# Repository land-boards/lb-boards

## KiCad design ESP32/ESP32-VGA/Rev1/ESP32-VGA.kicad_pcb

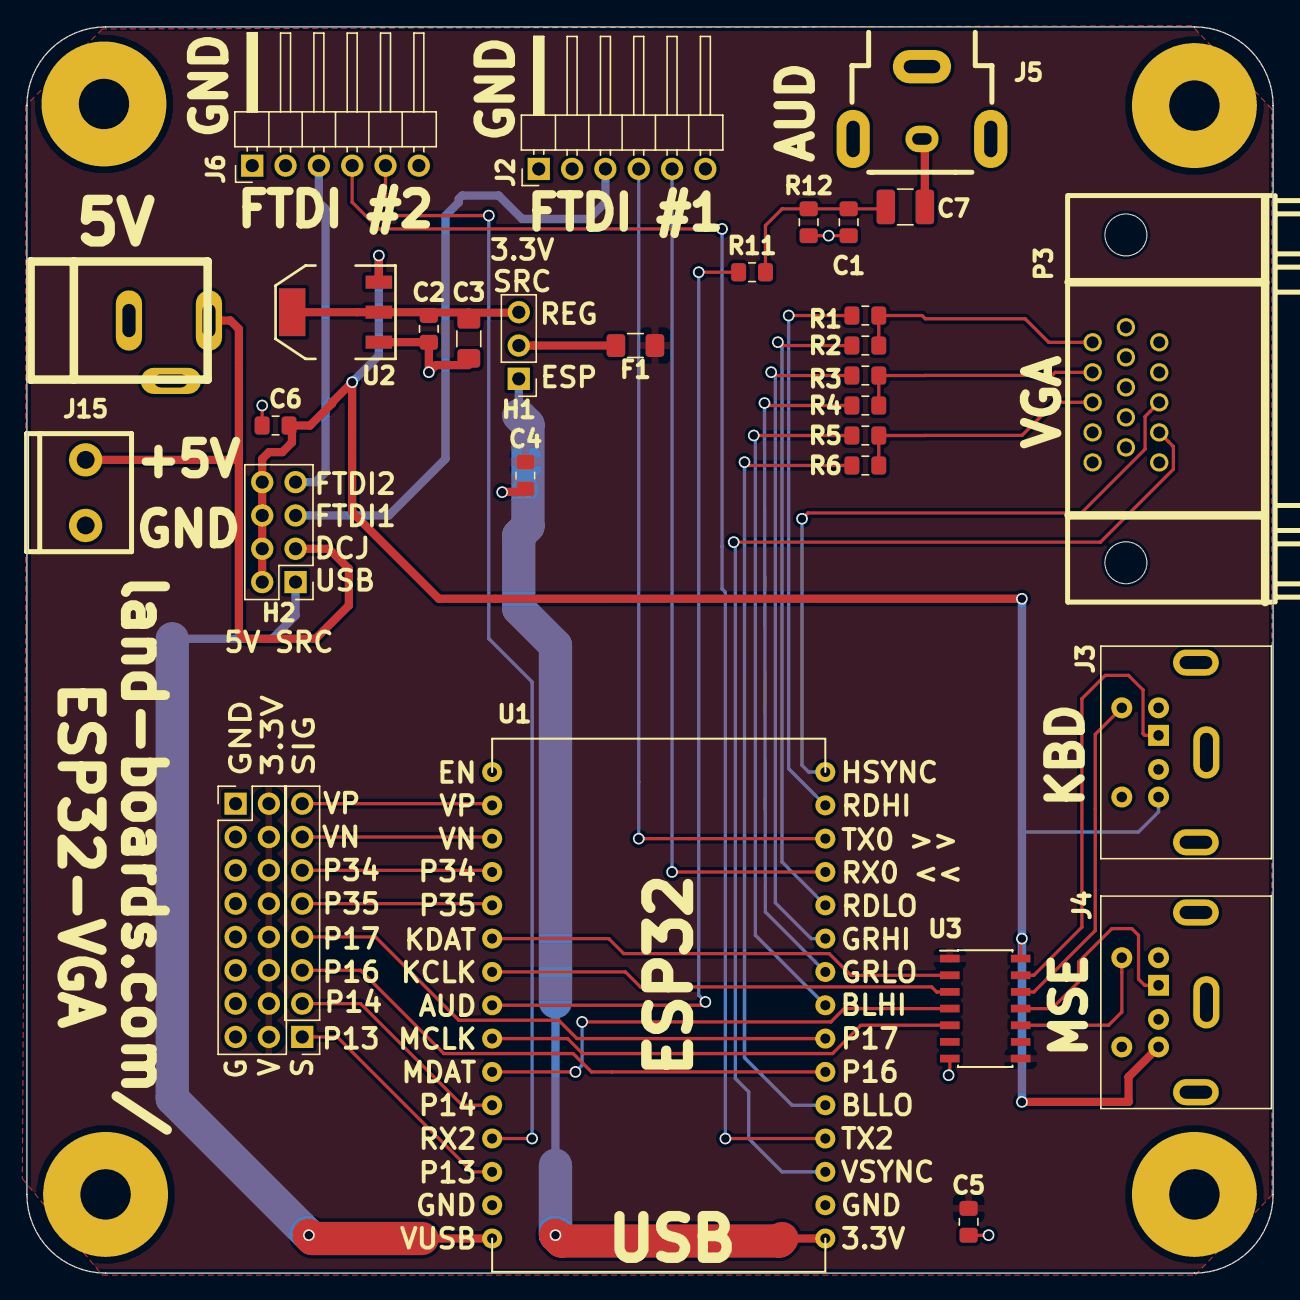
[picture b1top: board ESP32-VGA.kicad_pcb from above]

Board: 2 copper layers, 95.0 x 95.0 mm, 36 parts (0 on the bottom side), 44 nets.

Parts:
C1, C2, C4, C5, C6: 0.1uF; C_0805_2012Metric_Pad1.15x1.40mm_HandSolder
C3: 10uF; C_1206_3216Metric_Pad1.42x1.75mm_HandSolder
C7: CP1; C_1210_3225Metric_Pad1.42x2.65mm_HandSolder
F1: Polyfuse_Small; Fuse_1206_3216Metric_Pad1.42x1.75mm_HandSolder
H1: Conn_01x03; PinHeader_1x03_P2.54mm_Vertical
H2: Conn_02x04_Odd_Even; PinHeader_2x04_P2.54mm_Vertical
J1: DCJ0202; DCJ-NEW-Slotted
J2, J6: FTDI; PinHeader_1x06_P2.54mm_Horizontal
J3, J4: PS2_DIN6; Connector_Mini-DIN_Female_6Pin_2rows
J5: RCA-JACK; RCA
J15: Conn_01x02; TB2-5MM
MTG1, MTG2, MTG3: MTG_HOLE; MTG-6-32
MTG?1: MTG_HOLE; MTG-6-32
P2: Conn_02x08_Odd_Even; PinHeader_2x08_P2.54mm_Vertical
P3: VGA; DB_15F-VGA-fixed
P4: Conn_01x08; PinHeader_1x08_P2.54mm_Vertical
R1, R3, R5: 523; R_0805_2012Metric_Pad1.15x1.40mm_HandSolder
R2, R4, R6: 261; R_0805_2012Metric_Pad1.15x1.40mm_HandSolder
R11: 270; R_0805_2012Metric_Pad1.15x1.40mm_HandSolder
R12: 150; R_0805_2012Metric_Pad1.15x1.40mm_HandSolder
TEST1: COUPON; TEST_BLK-REAR
U1: ESP32; ESP32_EXP
U2: AP1117; SOT223
U3: TXS0104; SOIC-14_3.9x8.7mm_P1.27mm

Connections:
+3V3: C4.1, C5.1, F1.1, P2.2, P2.4, P2.6, P2.8, P2.10, P2.12, P2.14, P2.16, U3.1, U3.8
+5V: C6.1, H2.2, H2.4, H2.6, H2.8, J3.4, J4.4, U2.3, U3.14
/AUDIO: R11.2, U1.23
/BLUHI: R6.2, U1.5
/BLULO: R5.2, U1.8
/DCIN: H2.3, J1.1, J15.2
/ESP3V: H1.1, U1.1
/FTDI5V0: H2.5, J2.3
/FTDI5V2: H2.7, J6.3
/GP13: P4.1, U1.28
/GP14: P4.2, U1.26
/GP16: P4.3, U1.6
/GP17: P4.4, U1.7
/GP34: P4.6, U1.19
/GP35: P4.5, U1.20
/GRNHI: R4.2, U1.9
/GRNLO: R3.2, U1.10
/HSYNC: P3.13, U1.15
/KBCLK: U1.22, U3.3
/KBDAT: U1.21, U3.2
/MSECLK: U1.24, U3.5
/MSEDAT: U1.25, U3.4
/REDHI: R2.2, U1.11
/REDLO: R1.2, U1.14
/RX0: J2.5, U1.12
/RX2: J6.5, U1.27
/TX0: J2.4, U1.13
/TX2: J6.4, U1.4
/VN: P4.7, U1.18
/VO3: C2.1, C3.1, H1.3, U2.2, U2.4
/VP: P4.8, U1.17
/VSYNC: P3.14, U1.3
/VUSB: H2.1, U1.30
GND: C1.2, C2.2, C3.2, C4.2, C5.2, C6.2, J1.2, J1.3, J2.1, J3.3, J4.3, J5.1, J5.2, J5.3, J6.1, J15.1, P2.1, P2.3, P2.5, P2.7, P2.9, P2.11, P2.13, P2.15, P3.5, P3.6, P3.7, P3.8, P3.10, R12.1, U1.2, U1.29, U2.1, U3.7
unnamed: C1.1, C7.1, R11.1, R12.2
unnamed: C7.2, J5.4
unnamed: F1.2, H1.2
unnamed: J3.1, U3.13
unnamed: J3.5, U3.12
unnamed: J4.1, U3.11
unnamed: J4.5, U3.10
unnamed: P3.1, R1.1, R2.1
unnamed: P3.2, R3.1, R4.1
unnamed: P3.3, R5.1, R6.1

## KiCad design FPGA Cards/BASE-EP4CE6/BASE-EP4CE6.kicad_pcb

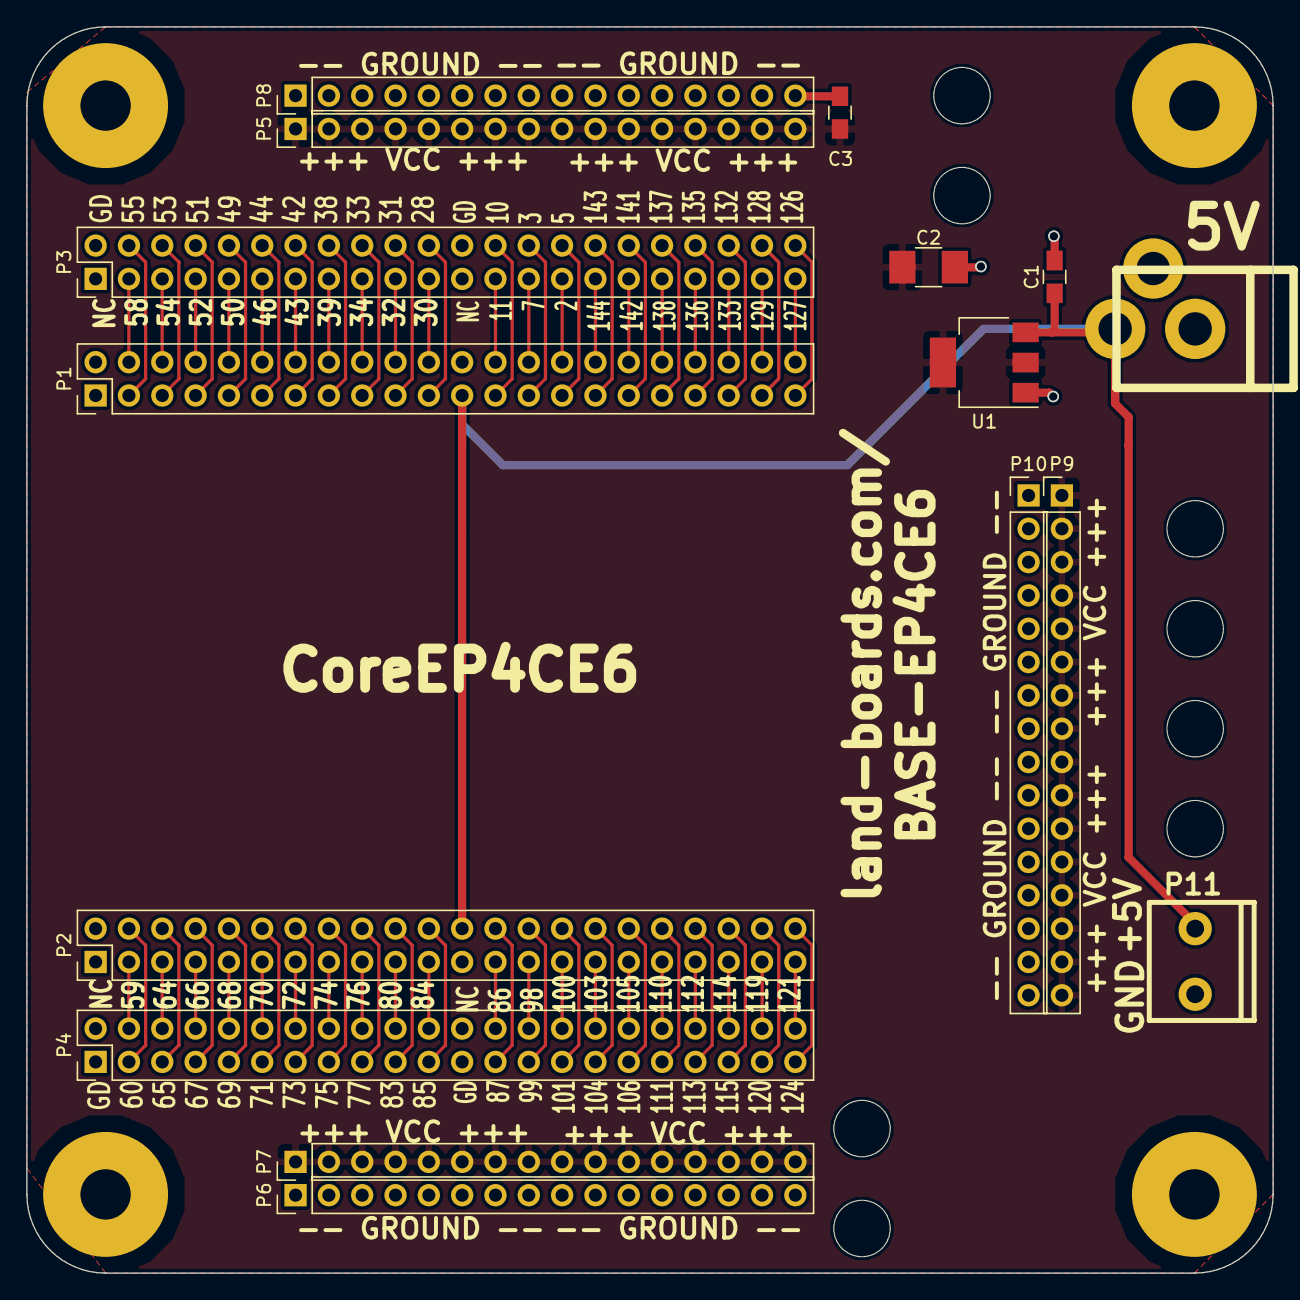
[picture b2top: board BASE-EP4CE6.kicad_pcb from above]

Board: 2 copper layers, 95.0 x 95.0 mm, 30 parts (0 on the bottom side), 83 nets.

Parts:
C1, C3: 0.1uF; C_0805_HandSoldering
C2: 10uF; C_1210_HandSoldering
COUP?1: COUPON; TEST_BLK-REAR
J1: DCJ0202; DCJ-NEW
MTG1, MTG2, MTG3: MTG_HOLE; MTG-6-32
MTG6, MTG7, MTG9, MTG10, MTG12, MTG13, MTG14, MTG15: MTG_HOLE; MountingHole_4.3mm_M4
MTG?1: MTG_HOLE; MTG-6-32
P1, P2, P3, P4: CONN_02X22; Pin_Header_Straight_2x22_Pitch2.54mm
P5, P6, P7, P8, P9, P10: CONN_01X16; Pin_Header_Straight_1x16_Pitch2.54mm
P11: CONN_01X02; TB2-5MM
TEST: COUPON; TEST_BLK-REAR
U1: AP1117; SOT-223

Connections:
+3V3: C2.1, C3.1, P5.1, P5.2, P5.3, P5.4, P5.5, P5.6, P5.7, P5.8, P5.9, P5.10, P5.11, P5.12, P5.13, P5.14, P5.15, P5.16, P7.1, P7.2, P7.3, P7.4, P7.5, P7.6, P7.7, P7.8, P7.9, P7.10, P7.11, P7.12, P7.13, P7.14, P7.15, P7.16, P9.1, P9.2, P9.3, P9.4, P9.5, P9.6, P9.7, P9.8, P9.9, P9.10, P9.11, P9.12, P9.13, P9.14, P9.15, P9.16, U1.2, U1.4
+5V: C1.1, J1.1, P1.23, P2.24, P11.1, U1.3
/P2: P1.30, P3.29
/P3: P1.27, P3.28
/P5: P1.29, P3.30
/P7: P1.28, P3.27
/P10: P1.25, P3.26
/P11: P1.26, P3.25
/P28: P1.21, P3.22
/P30: P1.22, P3.21
/P31: P1.19, P3.20
/P32: P1.20, P3.19
/P33: P1.17, P3.18
/P34: P1.18, P3.17
/P38: P1.15, P3.16
/P39: P1.16, P3.15
/P42: P1.13, P3.14
/P43: P1.14, P3.13
/P44: P1.11, P3.12
/P46: P1.12, P3.11
/P49: P1.9, P3.10
/P50: P1.10, P3.9
/P51: P1.7, P3.8
/P52: P1.8, P3.7
/P53: P1.5, P3.6
/P54: P1.6, P3.5
/P55: P1.3, P3.4
/P58: P1.4, P3.3
/P59: P2.3, P4.4
/P60: P2.4, P4.3
/P64: P2.5, P4.6
/P65: P2.6, P4.5
/P66: P2.7, P4.8
/P67: P2.8, P4.7
/P68: P2.9, P4.10
/P69: P2.10, P4.9
/P70: P2.11, P4.12
/P71: P2.12, P4.11
/P72: P2.13, P4.14
/P73: P2.14, P4.13
/P74: P2.15, P4.16
/P75: P2.16, P4.15
/P76: P2.17, P4.18
/P77: P2.18, P4.17
/P80: P2.19, P4.20
/P83: P2.20, P4.19
/P84: P2.21, P4.22
/P85: P2.22, P4.21
/P86: P2.25, P4.26
/P87: P2.26, P4.25
/P98: P2.27, P4.28
/P99: P2.28, P4.27
/P100: P2.29, P4.30
/P101: P2.30, P4.29
/P103: P2.31, P4.32
/P104: P2.32, P4.31
/P105: P2.33, P4.34
/P106: P2.34, P4.33
/P110: P2.35, P4.36
/P111: P2.36, P4.35
/P112: P2.37, P4.38
/P113: P2.38, P4.37
/P114: P2.39, P4.40
/P115: P2.40, P4.39
/P119: P2.41, P4.42
/P120: P2.42, P4.41
/P121: P2.43, P4.44
/P124: P2.44, P4.43
/P126: P1.43, P3.44
/P127: P1.44, P3.43
/P128: P1.41, P3.42
/P129: P1.42, P3.41
/P132: P1.39, P3.40
/P133: P1.40, P3.39
/P135: P1.37, P3.38
/P136: P1.38, P3.37
/P137: P1.35, P3.36
/P138: P1.36, P3.35
/P141: P1.33, P3.34
/P142: P1.34, P3.33
/P143: P1.31, P3.32
/P144: P1.32, P3.31
GND: C1.2, C2.2, C3.2, J1.2, J1.3, P1.2, P1.24, P2.1, P2.23, P3.2, P3.24, P4.1, P4.23, P6.1, P6.2, P6.3, P6.4, P6.5, P6.6, P6.7, P6.8, P6.9, P6.10, P6.11, P6.12, P6.13, P6.14, P6.15, P6.16, P8.1, P8.2, P8.3, P8.4, P8.5, P8.6, P8.7, P8.8, P8.9, P8.10, P8.11, P8.12, P8.13, P8.14, P8.15, P8.16, P10.1, P10.2, P10.3, P10.4, P10.5, P10.6, P10.7, P10.8, P10.9, P10.10, P10.11, P10.12, P10.13, P10.14, P10.15, P10.16, P11.2, U1.1

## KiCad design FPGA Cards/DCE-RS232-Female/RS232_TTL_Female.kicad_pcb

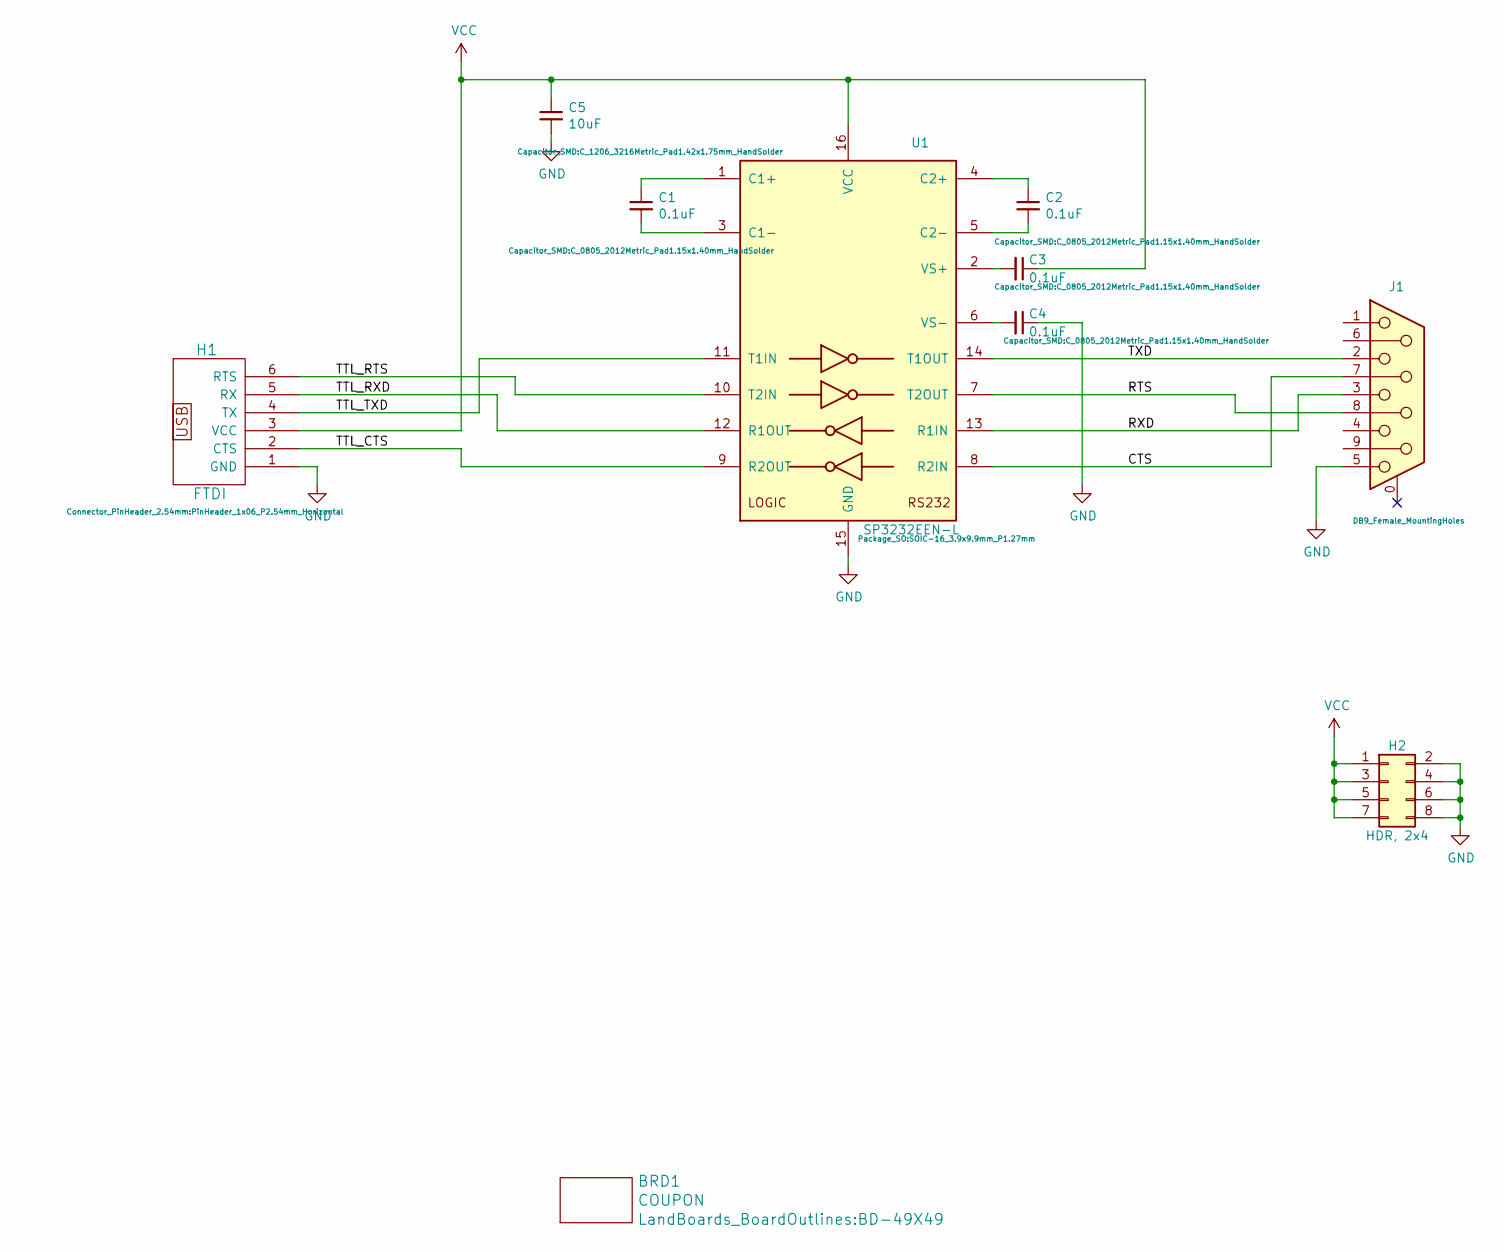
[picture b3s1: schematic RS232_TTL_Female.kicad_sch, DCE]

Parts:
BRD1: COUPON; BD-49X49
C1, C2, C3, C4: 0.1uF; C_0805_2012Metric_Pad1.15x1.40mm_HandSolder
C5: 10uF; C_1206_3216Metric_Pad1.42x1.75mm_HandSolder
H1: FTDI; PinHeader_1x06_P2.54mm_Horizontal
H2: HDR, 2x4; PinHeader_2x04_P2.54mm_Horizontal
J1: DB9_Female_MountingHoles; DSUB-9_Female_Horizontal_P2.77x2.84mm_EdgePinOffset4.94mm_H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
U1: SP3232EEN-L; SOIC-16_3.9x9.9mm_P1.27mm

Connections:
/CTS: J1.7, U1.8 (R2IN)
/RTS: J1.8, U1.7 (T2OUT)
/RXD: J1.3, U1.13 (R1IN)
/TTL_CTS: H1.2 (CTS), U1.9 (R2OUT)
/TTL_RTS: H1.6 (RTS), U1.10 (T2IN)
/TTL_RXD: H1.5 (RX), U1.12 (R1OUT)
/TTL_TXD: H1.4 (TX), U1.11 (T1IN)
/TXD: J1.2, U1.14 (T1OUT)
GND: C4.1, C5.2, H1.1 (GND), H2.2, H2.4, H2.6, H2.8, J1.5, U1.15 (GND)
unnamed: C1.1, U1.1 (C1+)
unnamed: C1.2, U1.3 (C1-)
unnamed: C2.1, U1.4 (C2+)
unnamed: C2.2, U1.5 (C2-)
unnamed: C3.2, U1.2 (VS+)
unnamed: C4.2, U1.6 (VS-)
VCC: C3.1, C5.1, H1.3 (VCC), H2.1, H2.3, H2.5, H2.7, U1.16 (VCC)

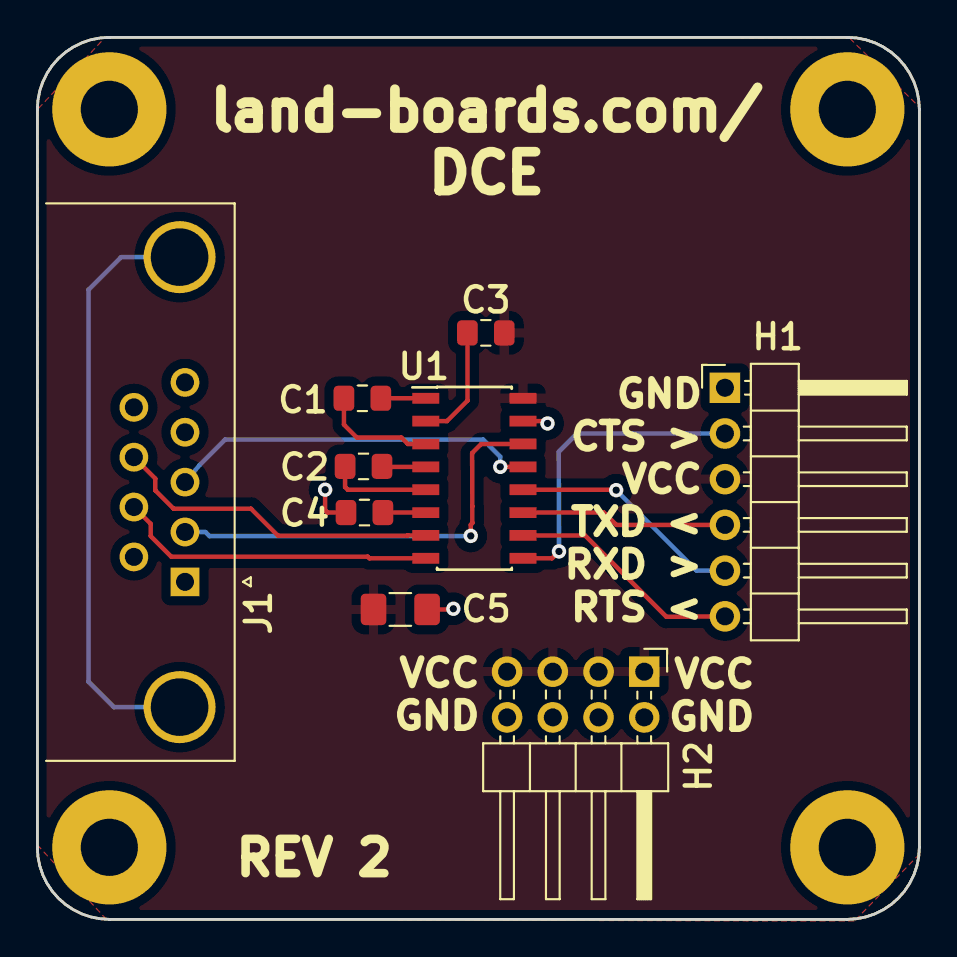
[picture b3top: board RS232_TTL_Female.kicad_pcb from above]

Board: 2 copper layers, 49.0 x 49.0 mm, 10 parts (0 on the bottom side), 16 nets.

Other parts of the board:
BD-49X49: VAL**; BD-49X49

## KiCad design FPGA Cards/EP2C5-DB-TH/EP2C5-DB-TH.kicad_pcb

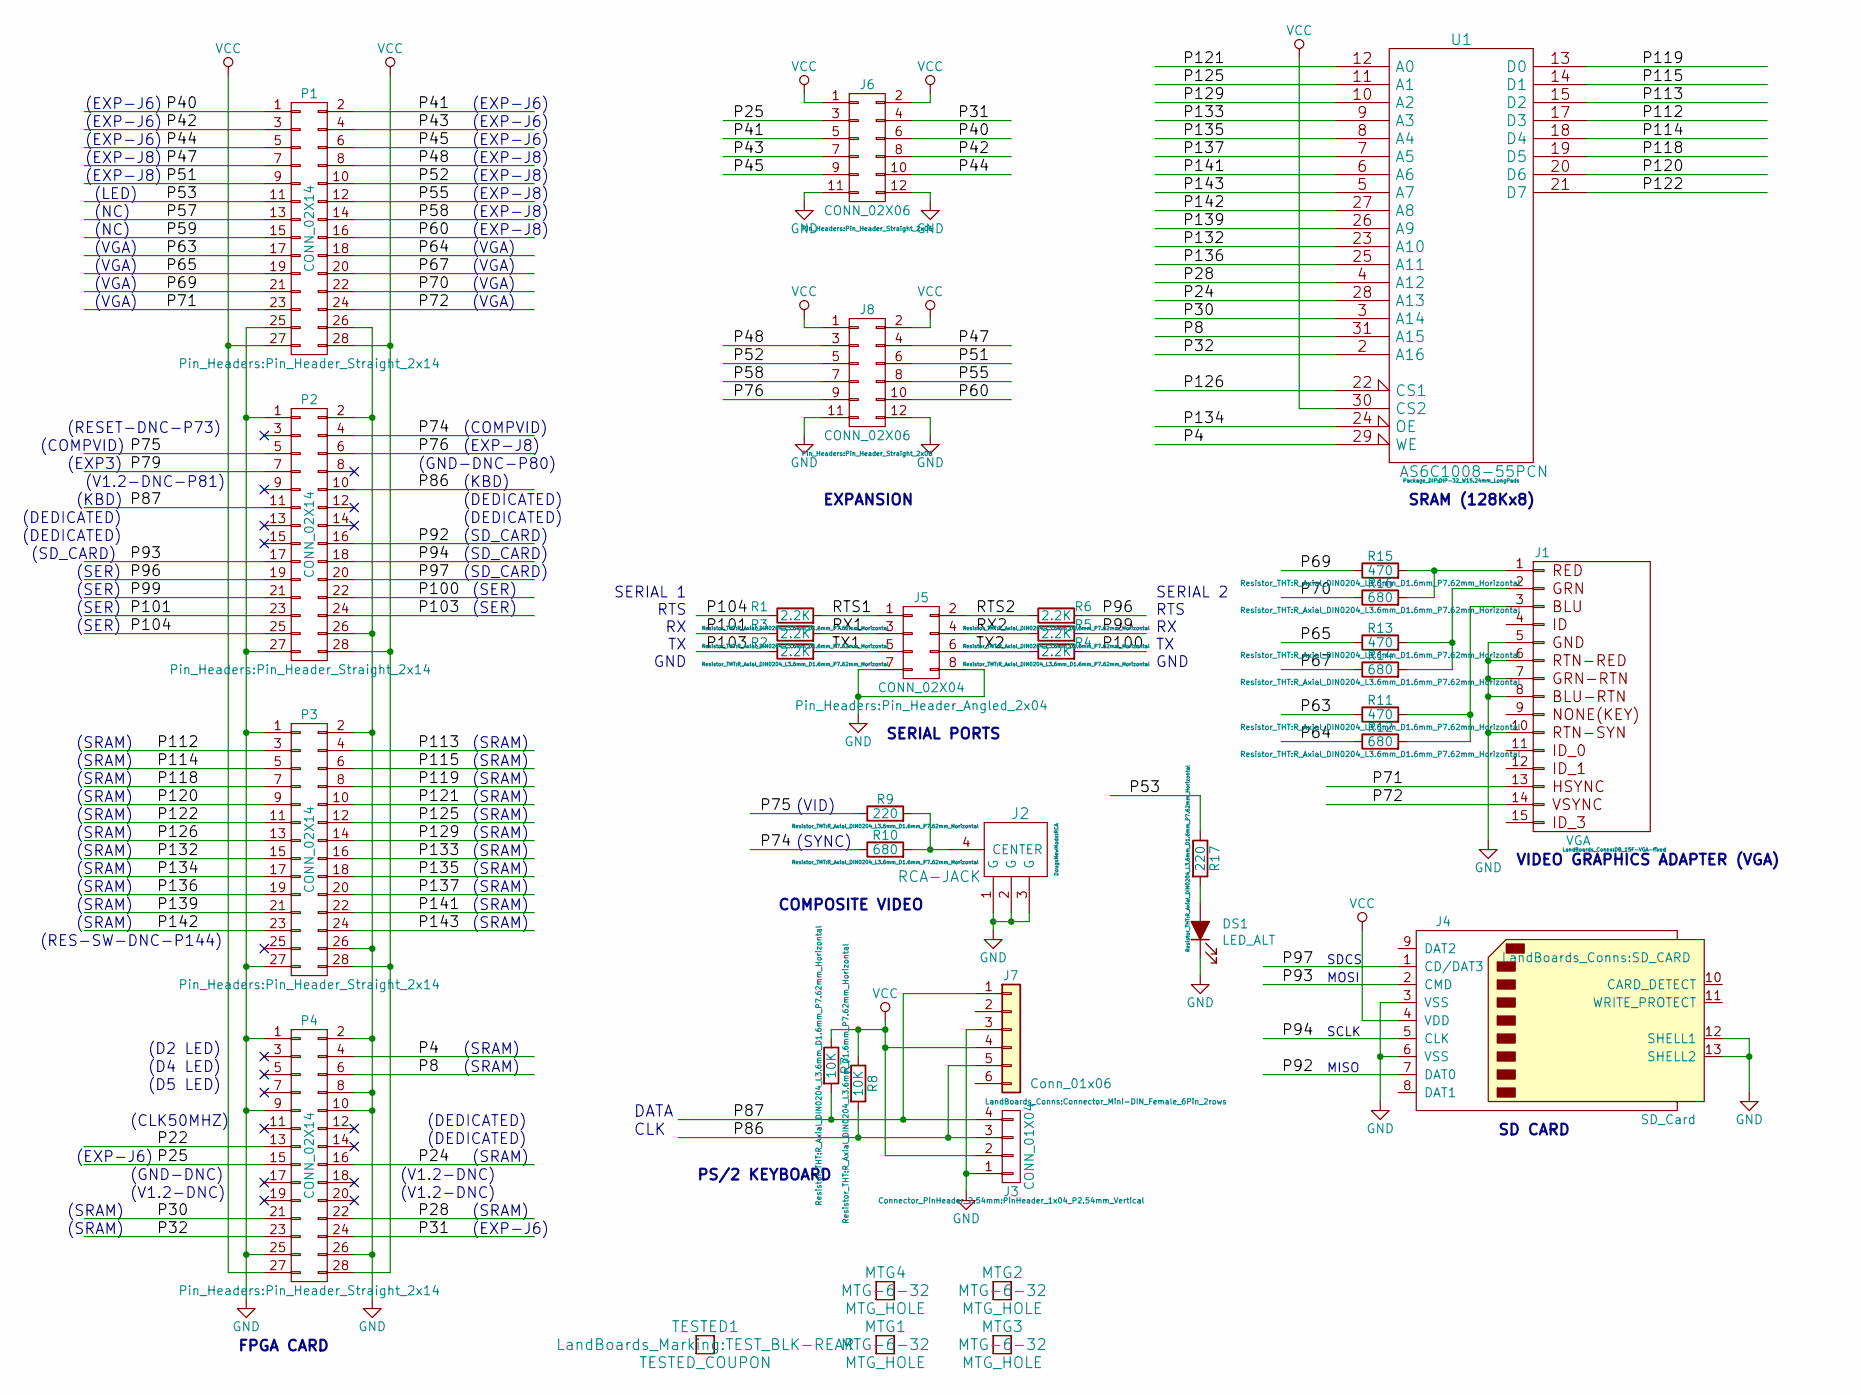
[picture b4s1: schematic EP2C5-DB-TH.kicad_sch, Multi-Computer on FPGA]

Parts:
DS1: LED_ALT; LED_D5.0mm
J1: VGA; DB_15F-VGA-fixed
J2: RCA-JACK; RCA
J3: CONN_01X04; PinHeader_1x04_P2.54mm_Vertical
J4: SD_Card; SD_CARD
J5: CONN_02X04; Pin_Header_Angled_2x04
J6, J8: CONN_02X06; Pin_Header_Straight_2x06
J7: Conn_01x06; Connector_Mini-DIN_Female_6Pin_2rows
MTG1, MTG2, MTG3, MTG4: MTG_HOLE; MTG-6-32
P1, P2, P3, P4: CONN_02X14; Pin_Header_Straight_2x14
R1, R2, R3, R4, R5, R6: 2.2K; R_Axial_DIN0204_L3.6mm_D1.6mm_P7.62mm_Horizontal
R7, R8: 10K; R_Axial_DIN0204_L3.6mm_D1.6mm_P7.62mm_Horizontal
R9, R17: 220; R_Axial_DIN0204_L3.6mm_D1.6mm_P7.62mm_Horizontal
R10, R12, R14, R16: 680; R_Axial_DIN0204_L3.6mm_D1.6mm_P7.62mm_Horizontal
R11, R13, R15: 470; R_Axial_DIN0204_L3.6mm_D1.6mm_P7.62mm_Horizontal
TESTED1: TESTED_COUPON; TEST_BLK-REAR
U1: AS6C1008-55PCN; DIP-32_W15.24mm_LongPads

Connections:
/P4: P4.4, U1.29 (WE)
/P8: P4.6, U1.31 (A15)
/P24: P4.16, U1.28 (A13)
/P25: J6.3, P4.15
/P28: P4.22, U1.4 (A12)
/P30: P4.21, U1.3 (A14)
/P31: J6.4, P4.24
/P32: P4.23, U1.2 (A16)
/P40: J6.6, P1.1
/P41: J6.5, P1.2
/P42: J6.8, P1.3
/P43: J6.7, P1.4
/P44: J6.10, P1.5
/P45: J6.9, P1.6
/P47: J8.4, P1.7
/P48: J8.3, P1.8
/P51: J8.6, P1.9
/P52: J8.5, P1.10
/P53: P1.11, R17.1
/P55: J8.8, P1.12
/P58: J8.7, P1.14
/P60: J8.10, P1.16
/P63: P1.17, R11.1
/P64: P1.18, R12.1
/P65: P1.19, R13.1
/P67: P1.20, R14.1
/P69: P1.21, R15.1
/P70: P1.22, R16.1
/P71: J1.13, P1.23
/P72: J1.14, P1.24
/P74: P2.4, R10.1
/P75: P2.5, R9.1
/P76: J8.9, P2.6
/P86: J3.3, J7.5, P2.10, R8.2
/P87: J3.4, J7.1, P2.11, R7.2
/P92: J4.7 (DAT0), P2.16
/P93: J4.2 (CMD), P2.17
/P94: J4.5 (CLK), P2.18
/P96: P2.19, R6.2
/P97: J4.1 (CD/DAT3), P2.20
/P99: P2.21, R5.2
/P100: P2.22, R4.2
/P101: P2.23, R3.1
/P103: P2.24, R2.1
/P104: P2.25, R1.1
/P112: P3.3, U1.17 (D3)
/P113: P3.4, U1.15 (D2)
/P114: P3.5, U1.18 (D4)
/P115: P3.6, U1.14 (D1)
/P118: P3.7, U1.19 (D5)
/P119: P3.8, U1.13 (D0)
/P120: P3.9, U1.20 (D6)
/P121: P3.10, U1.12 (A0)
/P122: P3.11, U1.21 (D7)
/P125: P3.12, U1.11 (A1)
/P126: P3.13, U1.22 (CS1)
/P129: P3.14, U1.10 (A2)
/P132: P3.15, U1.23 (A10)
/P133: P3.16, U1.9 (A3)
/P134: P3.17, U1.24 (OE)
/P135: P3.18, U1.8 (A4)
/P136: P3.19, U1.25 (A11)
/P137: P3.20, U1.7 (A5)
/P139: P3.21, U1.26 (A9)
/P141: P3.22, U1.6 (A6)
/P142: P3.23, U1.27 (A8)
/P143: P3.24, U1.5 (A7)
/RTS1: J5.1, R1.2
/RTS2: J5.2, R6.1
/RX1: J5.3, R3.2
/RX2: J5.4, R5.1
/TX1: J5.5, R2.2
/TX2: J5.6, R4.1
GND: DS1.1 (K), J1.5, J1.6, J1.7, J1.8, J1.10, J2.1 (G), J2.2 (G), J2.3 (G), J3.1, J4.3 (VSS), J4.6 (VSS), J4.12 (SHELL1), J4.13 (SHELL2), J5.7, J5.8, J6.11, J6.12, J7.3, J8.11, J8.12, P1.25, P1.26, P2.1, P2.2, P2.26, P2.27, P3.1, P3.2, P3.26, P3.27, P4.1, P4.2, P4.8, P4.9, P4.10, P4.25, P4.26, U1.16 (GND)
unnamed: DS1.2 (A), R17.2
unnamed: J1.1, R15.2, R16.2
unnamed: J1.2, R13.2, R14.2
unnamed: J1.3, R11.2, R12.2
unnamed: J2.4 (CENTER), R9.2, R10.2
VCC: J3.2, J4.4 (VDD), J6.1, J6.2, J7.4, J8.1, J8.2, P1.27, P1.28, P2.28, P3.28, P4.27, P4.28, R7.1, R8.1, U1.30 (CS2), U1.32 (VCC)

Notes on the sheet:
VIDEO GRAPHICS ADAPTER (VGA)
(SER)
(NC)
(SRAM)
(EXP-J8)
SCLK
(VGA)
(D4 LED)
MOSI
(SD_CARD)
FPGA CARD
(V1.2-DNC-P81)
(DEDICATED)
MISO
(D2 LED)
(EXP-J6)
(EXP3)
(RESET-DNC-P73)
(CLK50MHZ)
COMPOSITE VIDEO
EXPANSION
(VID)
SERIAL PORTS
(COMPVID)
(SYNC)
SERIAL 2 RTS RX TX GND
SRAM (128Kx8)
(D5 LED)
(KBD)
SD CARD
(GND-DNC-P80)
(V1.2-DNC)
DATA CLK
(LED)
SDCS
SERIAL 1 RTS RX TX GND
(RES-SW-DNC-P144)
PS/2 KEYBOARD
(GND-DNC)

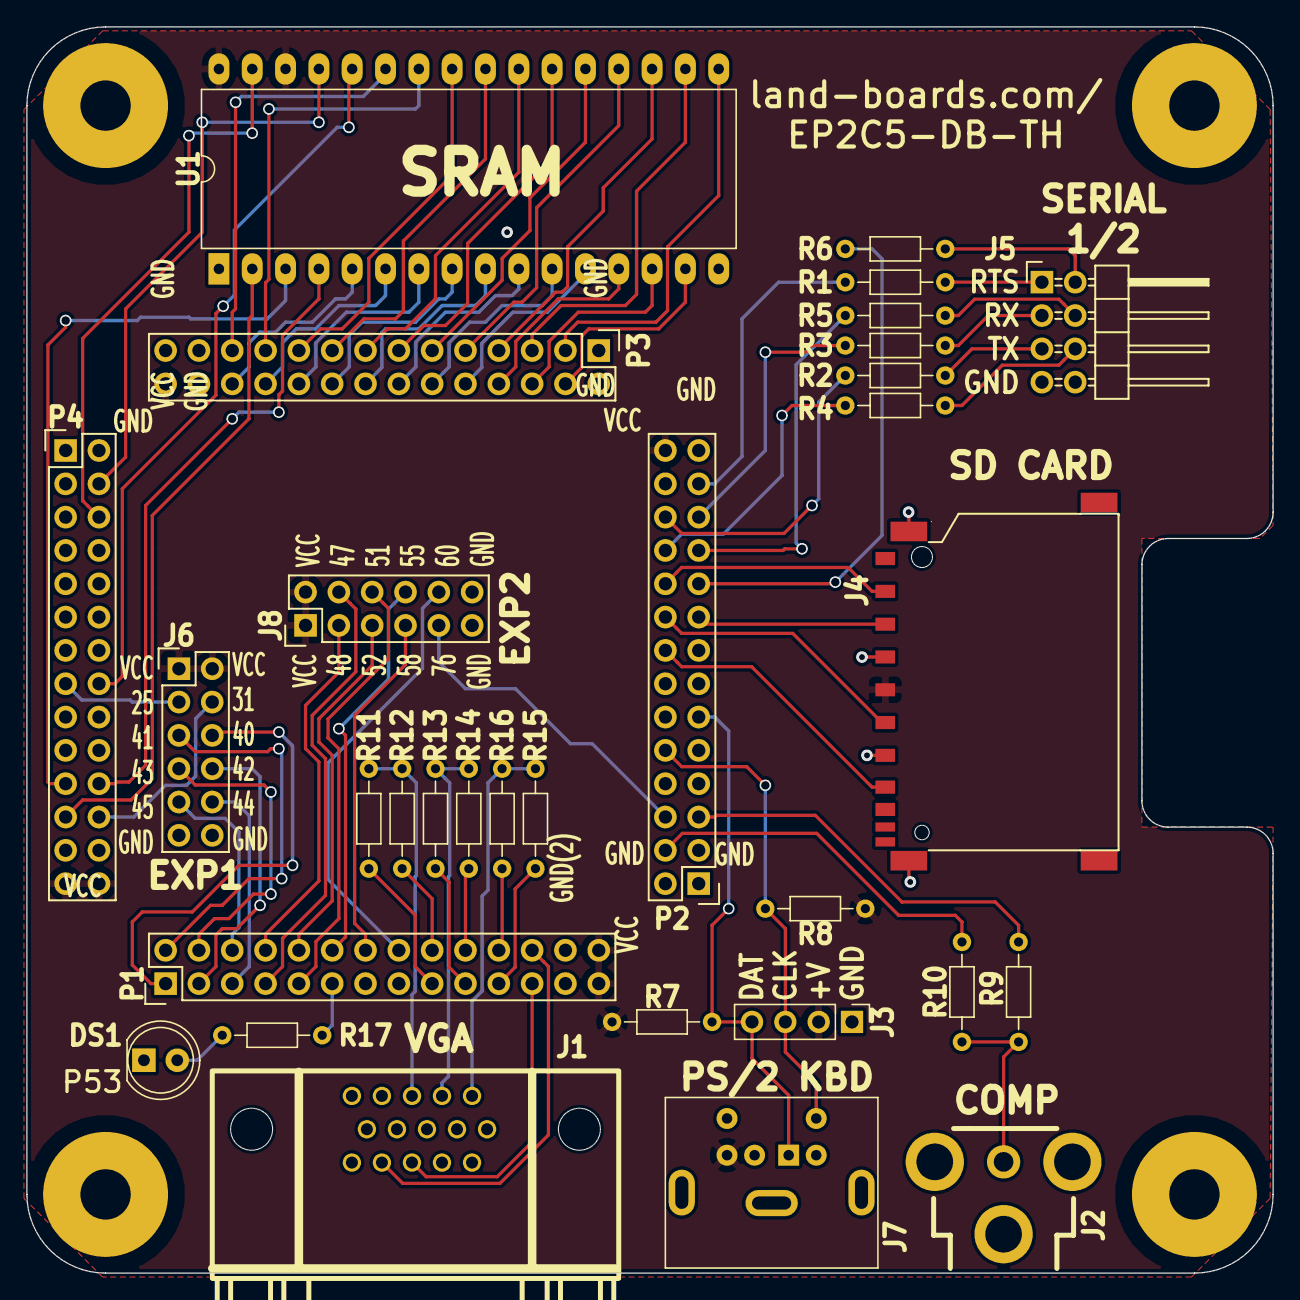
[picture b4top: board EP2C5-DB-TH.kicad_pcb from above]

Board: 2 copper layers, 95.0 x 95.0 mm, 35 parts (0 on the bottom side), 80 nets.
